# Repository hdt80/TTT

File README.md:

# Tabletop token tracker

Embedded senior project

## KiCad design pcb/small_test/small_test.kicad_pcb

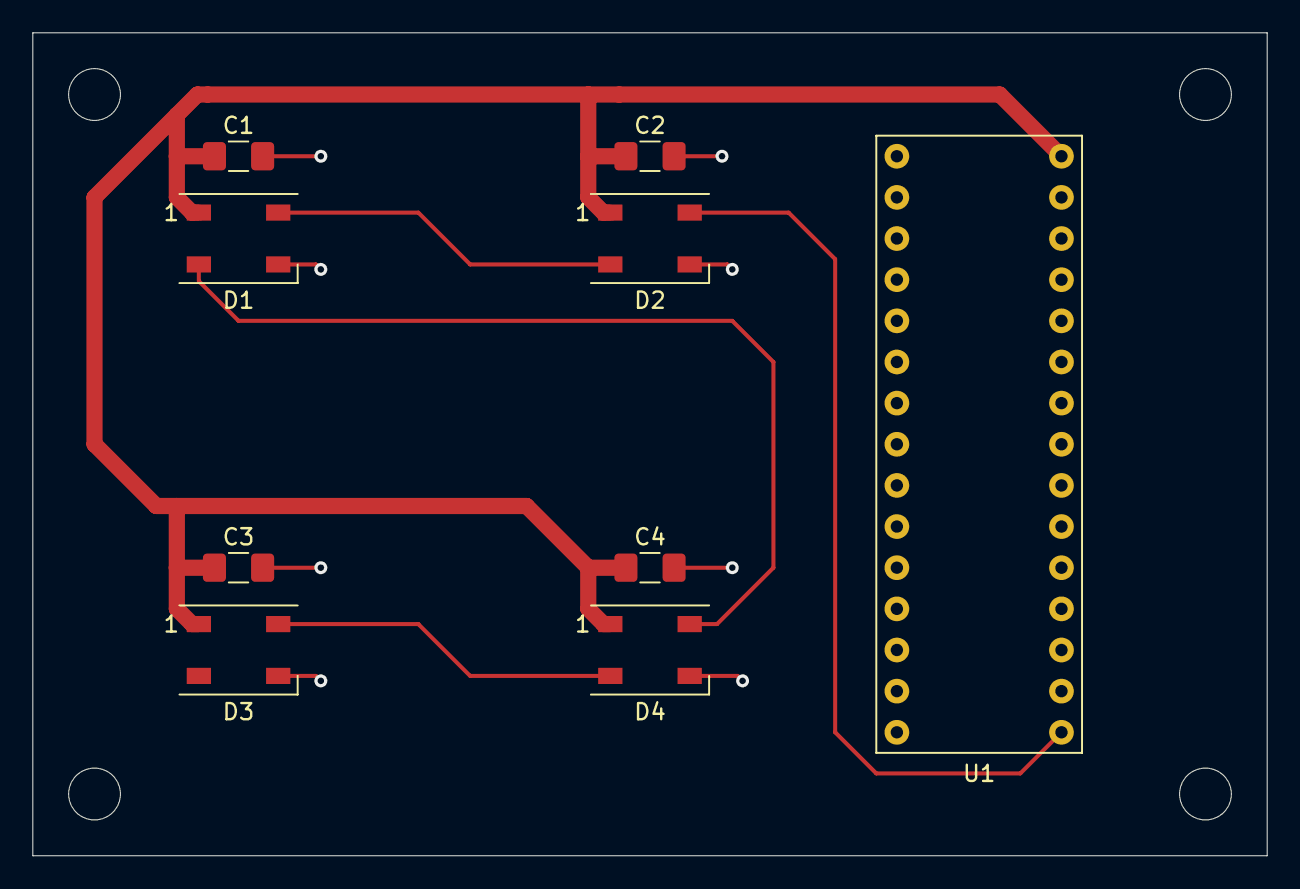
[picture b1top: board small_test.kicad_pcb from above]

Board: 2 copper layers, 76.2 x 50.8 mm, 9 parts (0 on the bottom side), 6 nets.

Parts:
C1, C2, C3, C4: C; C_1206_3216Metric_Pad1.42x1.75mm_HandSolder
D1, D2, D3, D4: Neopixel5050; LED_WS2812B_PLCC4_5.0x5.0mm_P3.2mm
U1: ArduinoNano_r3.3; ArduinoNano.r3_3

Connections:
GND: C1.1, C2.1, C3.1, C4.1, D1.3, D2.3, D3.3, D4.3, U1.29
G_VCC: C1.2, C2.2, C3.2, C4.2, D1.1, D2.1, D3.1, D4.1, U1.30
LED_DATA: D2.4, U1.16
LED_R0t1: D1.2, D4.4
unnamed: D1.4, D2.2
unnamed: D3.4, D4.2

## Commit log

2019-10-22 Add initial test project using Arduino
2019-10-22 Update test code to use two analog inputs
2019-10-22 Update LICENSE
2019-10-29 Add /docs, which contains development on TTT
    Add communication, detailing how the two components of TTT will talk to each other
2019-10-29 Try to fix docs/communication table formatting
2019-10-29 Add more software message details
2019-10-29 Update communication
2019-10-29 Add missing table row
2019-10-29 Add logging entry notes
2019-10-29 Add examples to communication notes
2019-10-29 Change responses. Rename communication to messages
2019-11-11 Update firmware and SDK
2019-11-12 Change software writing to use the fd as a tty instead of as a file
2019-11-25 Implement RGB LED module
2019-12-03 Add data from testing maximum power drawn
2019-12-08 Implement software LED control
2019-12-08 Update commands documentation
2019-12-08 Update command specification
2020-01-27 Add PCB files
2020-01-28 Begin work on small PCB test
2020-01-28 Update test PCB with new symbols and added caps
2020-01-29 Update test PCB
2020-02-09 Implement grid get command
2020-03-07 Change communication protocol to use timeout for end of message. Implement voltage grid sensor, will update to resistor.
2020-03-08 Implement ADC demo
2020-05-04 Add GUI part of project
2020-06-02 Add software GUI
